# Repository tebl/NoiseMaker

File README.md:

# NoiseMaker
When I first started out with my somewhat weird hobby of working with seriously to extremely outdated computers, the first things to go were naturally the inevitably failing hard-drives that ended up being replaced by Compact Flash solutions. The second to go were the physical floppy disk drives, having been replaced by Gotek drives. The result, while enjoyable to use, were vintage computers that even the wife could even stand to listen to. Except... that's not good, they're supposed to go *whirr*, *click*, *whine* and rotate grinding gears at such a rate that your significant other simply won't just accept a room dedicated to your vintage computers, they should demand that you get started on building such a room!

Was I going back to the old failiure rate of old mechanical drives? Nope, I followed the tutorials and installed a buzzer kit on that Gotek. Was I happy with it? Not really. So I did what I tend to do, go on AliExpress and ordered a bucketload of Arduino-modules listed as capable of playing back sound files. The cheapest of the bunch by far, was the *MP3-TF-16P* - also commonly known as the *DFPlayer Mini*. The very next thing that I discovered was that I didn't really understand enough about the various signals used to communicate with floppy disk drives, so they all sat in box somewhere until someone created something called *HDD Clicker*. I saw the videos made about it, but I wanted more options and so I started tinkering with the modules again - especially with the realization of how simple an IDE-version could have been made if I had just started there instead.

The result was this project, an amalgamation of the cheapest hardware in an oversized package that somehow probably ends up costing several times more to build than the popular thing. I could certainly have gone for more compact or powerful options, but it was an excuse to use some  Arduino Nano boards "powered" by ATmega168, which I had accidentally ordered a couple of years ago and never got around to throwing out.

- [1> Modules](#1-modules)
  - [1.1> NoiseMaker Standard](#11-noisemaker-standard)
- [3> Acknowledgements](#3-acknowledgements)

# 1> Modules
The following modules have been provided as part of this project. While more modules may have been included as part of this repository, these are the ones that I have actually built and tested. As mentioned in the relevant license for this project - that's not a warranty, just an indication that it worked that one time I tried it with my particular setup.

| Module                            | Description                                      |
| --------------------------------- | ------------------------------------------------ | 
| [NoiseMaker Standard](#11-noisemaker-standard) | Standard Arduino-based *NoiseMaker*, supporting 34-pin floppy and 40-pin IDE.

## 1.1> NoiseMaker Standard
This is the standard version of the *NoiseMaker*, created as a carrier board for both the *MP3-TF-16P* and an Arduino Nano. It can be built to work directly with IDE-devices, adding a female 40-pin header to the bottom of the card it can also be attached directly onto common *Compact Flash to IDE*-module. It can also be used in the "middle" of the cable, or just plugged into an unused part of the cable. The Arduino unfortunately doesn't have anywhere near the capability needed to actually interpret the communication between the devices, it is only responding to the same signal that your motherboard would normally read in order to light up your *HDD LED* (if you have one). 

 Alternatively you can build the device for use with 34-pin floppy drive replacements such as the Gotek instead. Similarly as with the IDE-version, it can also be plugged into an unused connector on your cable or in-between your drive and motherboard. Note that since the 34-pin cables have a twist on it, you need to set the *DRV_SEL* to the opposite value if connecting it up by itself after the twist.

The documentation belonging to different variations of the standard NoiseMaker have been listed below, click the name for build documentation or follow the documentation links to jump to different sections within it. Ideally all of them should support being built as a NoiseMaker for either floppy or IDE, but not both at the same time (for that you will need two separate copies of the PCB).

| Module                 | Description                        | Documentation                      | Order      |
| ---------------------- | ---------------------------------- | ---------------------------------- | ---------- |
| [NoiseMaker](https://github.com/tebl/NoiseMaker/tree/main/NoiseMaker) | Arduino Nano, MP3-TF-16P | [Documentation](https://github.com/tebl/NoiseMaker/tree/main/NoiseMaker), [BOM](https://github.com/tebl/NoiseMaker/blob/main/NoiseMaker/README.md#3-bom), [Setting it up](https://github.com/tebl/NoiseMaker/blob/main/documentation/setting_it_up.md), [Getting started](https://github.com/tebl/NoiseMaker/blob/main/documentation/getting_started.md) | PCBWay

# 3> Acknowledgements
Everything comes from something, in particular when it comes to most of my electronics projects. I mainly build things I would like to own, often doing a respin to fit my own particular style and preferences. As mentioned I originally started making a module for making noise when used with modern floppy drive replacements, but it was only with inspiration from seeing the *HDD Clicker* that I went back and actually finished building it.

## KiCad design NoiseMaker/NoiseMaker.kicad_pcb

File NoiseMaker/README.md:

# NoiseMaker Standard
The *NoiseMaker Standard*-version is really the first version I created for making noise when used with either 34-pin floppy drive replacements such as the Gotek - OR - the 40-pin IDE-replacements such as CF2IDE, SD2IDE etc. This document goes into building up a PCB for one of these, but not both at a time. For a more graceful introduction to what the *NoiseMaker* is meant to do, check out the main [documentation](https://github.com/tebl/NoiseMaker) before continuing.

- [1> Building the device](#1-building-the-device)
  - [1.1> Soldering it together](#11-soldering-it-together)
  - [1.2> IDE-version](#12-ide-version)
  - [1.3> Floppy-version](#13-floppy-version)
  - [1.4> Finishing touches](#14-finishing-touches)
- [2> Schematic](#2-schematic)
- [3> BOM](#3-bom)

# 1> Building the device
Building a device such as this assumes you have at least minor experience soldering things together, recommended is that you at the very least have access to a soldering station with adjustable temperature. If currently available, you should probably start with 60/40 rosin core solder as the lead-free alternatives tends to be a bit harder to work with.

With the requirements for basic equipment sorted, we need to talk a bit about what you want to achieve while building this project. The reason I ask is that as already mentioned, you need to pick between Floppy and IDE for each PCB you are building up, mainly because there are physical differences in how each of them connect to the your system. 

Now that you know what you want to build, we can get started on the most expensive step in any build process - shopping! So, head on over to the [BOM](#3-bom)-section for some information on what kind of components that you'll need. While I would have liked to give you specific part numbers for "reputable" electronic part suppliers, I can't afford to shop there so I usually make due with what I can find on sites such as ebay, AliExpress and any similar sites that sell cheap Chinese components. The downside to this is that I can't link to a part directly and expect it to stay listed, so you'll need to consider the description listed as a suggested *search term*.

## 1.1> Soldering it together
The construction of this unit should be fairly straight-forward, just take your time in order to make sure everything goes into place - more or less straight. I usually recommend starting by having a good look at the PCBs, then try to figure out where all of the listed components go and in which orientation they go in (all of this should be clearly marked on the silkscreen). There are no overlapping footprints and though doing it in the wrong order might make it a bit more fiddly to put together, there aren't really all that many issues you can run into as long as you're clear on which interface you're building it for (IDE or floppy). 

## 1.2> IDE-version
I've created a video that goes into whatever details you might need when assembling one for use with IDE, this one specificly was built to mount directly onto a common *Compact Flash*-adapter and for that reason I solder the power wires directly to it instead of using an additional floppy power connector from the systems PSU.

## 1.3> Floppy-version
For now I recommend that you check the build details for the IDE-version, it is mostly the same except for the use of 34-pin Interface.

## 1.4> Finishing touches
Unless one was provided to you by a kit-maker, you will more than likely not have the correct firmware installed on your Arduino Nano. The code you need can be found as part of this repository on the URL [software/arduino/NoiseMaker](https://github.com/tebl/NoiseMaker/tree/main/software/arduino/NoiseMaker), you will need to download a copy of this repository - this is done by using the green button on the [main page](https://github.com/tebl/NoiseMaker) of this repository. You will need to install a couple of libraries in order for the code to compile, the [README](https://github.com/tebl/NoiseMaker/blob/main/software/arduino/NoiseMaker/README.md) contains links to both of these though the preferable way of installing these is probably via your Arduino development environment. The files provided should be suitable for use with both Arduino Studio as well as PlatformIO.

For Arduino Studio, open the sketch and then select the board that you have (Arduino Nano of some kind). Install the two libraries from *Tools* --> *Manage libraries...* - search for and install the two listed as *ezbutton* as well as *DFRobotDFPlayerMini*. Check that the code now compiles, select the serial port corresponding to your module and upload the sketch.

PlatformIO should handle dependencies somewhat automatically, though I find that in practice we need to run a command for it to happen. Open up a new PlatformIO Terminal (not PowerShell, it's probably the last icon on your bottom toolbar), then run the command *"pio pkg install"*, and it should download and install the latest version of the libraries needed. Ensure that the environment selected on the bottom toolbar corresponds to the board you are using, you may need to edit *platformio.ini* if neither of the combinations is correct for you. Compile and upload the code.

Using a serial terminal connected to the Arduino Nano, you may configure the device according to your preferences. It is recommended to use an ATmega328-based Arduino Nano when you are familiarizing yourself with the commands, as among other commands the *help* command is not available on the ATmega168. When satisfied with any changes, enter the command *save* to store them permanently to the onboard EEPROM. For more detailed information as well as serving as a reference when used with ATmega168, see [Serial Interface](https://github.com/tebl/NoiseMaker/blob/main/documentation/serial_interface.md).

# 2> Schematic
The supplied KiCad files should be sufficient as both a schematic and as a  starting point for ordering PCBs (basically you could just zip the contents of the export folder and upload that on a fabrication site), the schematic is also available in [PDF-format](https://github.com/tebl/NoiseMaker/tree/main/documentation/schematic) and this is what you'll need to print and work your way through this things don't work as expected after assembly.

# 3> BOM
Most parts should be easy to get a hold of from your favourite local electronic component shop, but given that I don't have access to such shops where I live so everything was based on whatever I could get cheapest from eBay/AliExpress (free shipping, but plan on waiting 3-4 weeks for delivery). Components in parenthesis can be considered optional for features beyond the more basic functionality, but where's the fun in that? You probably want the complete package.

| Reference             | Item                                                              | Count | Order  |
| --------------------- | ----------------------------------------------------------------- | ----- | ------ |
| NoiseMaker Standard   | Fabricate using Gerber files                                      |     1 | [PCBWay](https://www.pcbway.com/project/shareproject/NoiseMaker_IDE_Floppy_8a4ab037.html)
| A1 *                  | Arduino Nano (328, 168 with less features)                        |     1 |
| A2 *                  | MP3-TF-16P (also known as DFPlayer Mini)                          |     1 |
| D1                    | 1N5819 (DO-41), 1N4001 if you don't have one available            |     1 |
| J1 **                 | 2x20pin female header, 2x20pin male header or 2x17pin male header |     1 |
| J2 **                 | 2x20pin male header or 2x17pin male header                        |     1 |
| J3 ***                | JVC Mini 4P, right-angle flat power connector for floppy          |     1 |
| J4                    | 4pin breakable right-angle header                                 |    (1)|
| JP1, JP2              | 3pin straight pin header                                          |     2 |
|                       | Jumper cap                                                        |     2 |
| LS1                   | Passive buzzer (7.62mm pin spacing)                               |    (1)|
| R1                    | 1k Ohm resistor                                                   |     1 |
| SW1-SW3               | 6x6mm momentary button                                            |    (3)|

*) Both of the modules will be soldered to the PCB with some straight male headers in between, when assembling the first unit it is recommend that you assemble it with female pin headers on the board so that modules can be moved around until happy with the results.

**) The type of header used here depends on what the board will be used as, 2x16pin are for floppy while 2x20pin are for IDE.

***) When installed directly on top of a Compact Flash adapter you can opt to wire it directly to the adapter. If you can't find the connector, it might be easier to find a floppy power splitter cable, cut and solder on the wires from that.

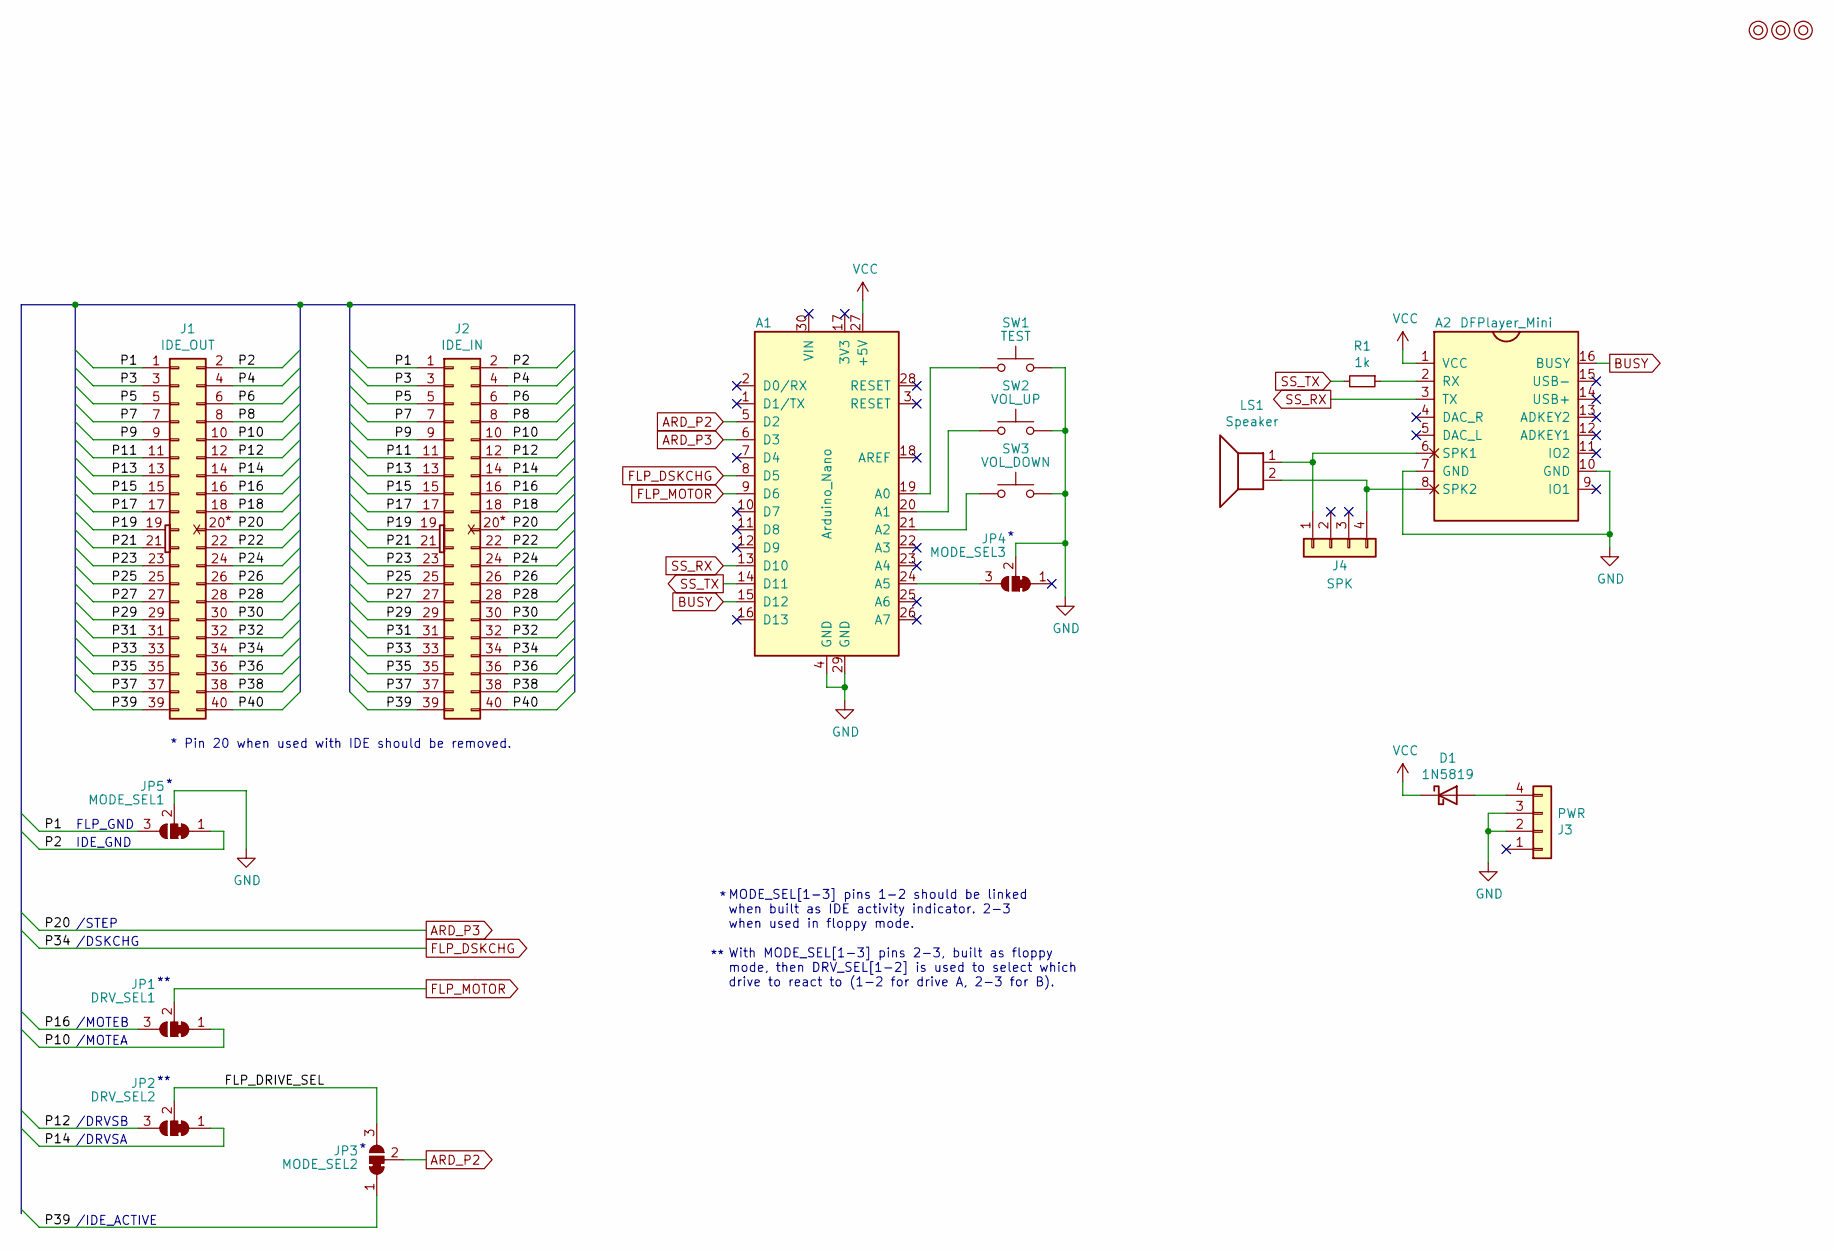
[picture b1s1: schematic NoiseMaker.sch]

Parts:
A1: Arduino_Nano
A2: DFPlayer_Mini
D1: 1N5819; D_DO-41_SOD81_P12.70mm_Horizontal
J1: IDE_OUT; PinSocket_2x20_P2.54mm_Vertical
J2: IDE_IN; IDC-Header_2x20_P2.54mm_Vertical
J3: PWR; Molex_KK-254_1x04_P2.54mm_Horizontal
J4: SPK; PinHeader_1x04_P2.54mm_Horizontal
JP1: DRV_SEL1; PinHeader_1x03_P2.54mm_Vertical
JP2: DRV_SEL2; PinHeader_1x03_P2.54mm_Vertical
JP3: MODE_SEL2; select2
JP4: MODE_SEL3; select2
JP5: MODE_SEL1; select2
LS1: Speaker; Buzzer_12x9.5RM7.6
M1, M2, M3: Mounting; M3_pin
R1: 1k; R_Axial_DIN0207_L6.3mm_D2.5mm_P10.16mm_Horizontal
SW1: TEST; SW_PUSH_6mm
SW2: VOL_UP; SW_PUSH_6mm
SW3: VOL_DOWN; SW_PUSH_6mm

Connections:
/FLP_DRIVE_SEL: JP2.2 (C), JP3.3 (B)
/P1: J1.1, J2.1, JP5.3 (B)
/P2: J1.2, J2.2, JP5.1 (A)
/P3: J1.3, J2.3
/P4: J1.4, J2.4
/P5: J1.5, J2.5
/P6: J1.6, J2.6
/P7: J1.7, J2.7
/P8: J1.8, J2.8
/P9: J1.9, J2.9
/P10: J1.10, J2.10, JP1.1 (A)
/P11: J1.11, J2.11
/P12: J1.12, J2.12, JP2.3 (B)
/P13: J1.13, J2.13
/P14: J1.14, J2.14, JP2.1 (A)
/P15: J1.15, J2.15
/P16: J1.16, J2.16, JP1.3 (B)
/P17: J1.17, J2.17
/P18: J1.18, J2.18
/P19: J1.19, J2.19
/P21: J1.21, J2.21
/P22: J1.22, J2.22
/P23: J1.23, J2.23
/P24: J1.24, J2.24
/P25: J1.25, J2.25
/P26: J1.26, J2.26
/P27: J1.27, J2.27
/P28: J1.28, J2.28
/P29: J1.29, J2.29
/P30: J1.30, J2.30
/P31: J1.31, J2.31
/P32: J1.32, J2.32
/P33: J1.33, J2.33
/P35: J1.35, J2.35
/P36: J1.36, J2.36
/P37: J1.37, J2.37
/P38: J1.38, J2.38
/P39: J1.39, J2.39, JP3.1 (A)
/P40: J1.40, J2.40
ARD_P2: A1.5 (D2), JP3.2 (C)
ARD_P3: A1.6 (D3), J1.20, J2.20
BUSY: A1.15 (D12), A2.16 (BUSY)
FLP_DSKCHG: A1.8 (D5), J1.34, J2.34
FLP_MOTOR: A1.9 (D6), JP1.2 (C)
GND: A1.4 (GND), A1.29 (GND), A2.7 (GND), A2.10 (GND), J3.2, J3.3, JP4.2 (C), JP5.2 (C), SW1.2, SW2.2, SW3.2
unnamed: A1.19 (A0), SW1.1
unnamed: A1.20 (A1), SW2.1
unnamed: A1.21 (A2), SW3.1
unnamed: A1.24 (A5), JP4.3 (B)
unnamed: A2.2 (RX), R1.1
unnamed: A2.6 (SPK1), J4.1, LS1.1
unnamed: A2.8 (SPK2), J4.4, LS1.2
unnamed: D1.2 (A), J3.4
SS_RX: A1.13 (D10), A2.3 (TX)
SS_TX: A1.14 (D11), R1.2
VCC: A1.27 (+5V), A2.1 (VCC), D1.1 (K)

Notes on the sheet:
/DRVSA
/DRVSB
/MOTEA
/MOTEB
/IDE_ACTIVE
/STEP
/DSKCHG
* Pin 20 when used with IDE should be removed.
IDE_GND
FLP_GND
MODE_SEL[1-3] pins 1-2 should be linked when built as IDE activity indicator. 2-3 when used in floppy mode.
With MODE_SEL[1-3] pins 2-3, built as floppy mode, then DRV_SEL[1-2] is used to select which drive to react to (1-2 for drive A, 2-3 for B).

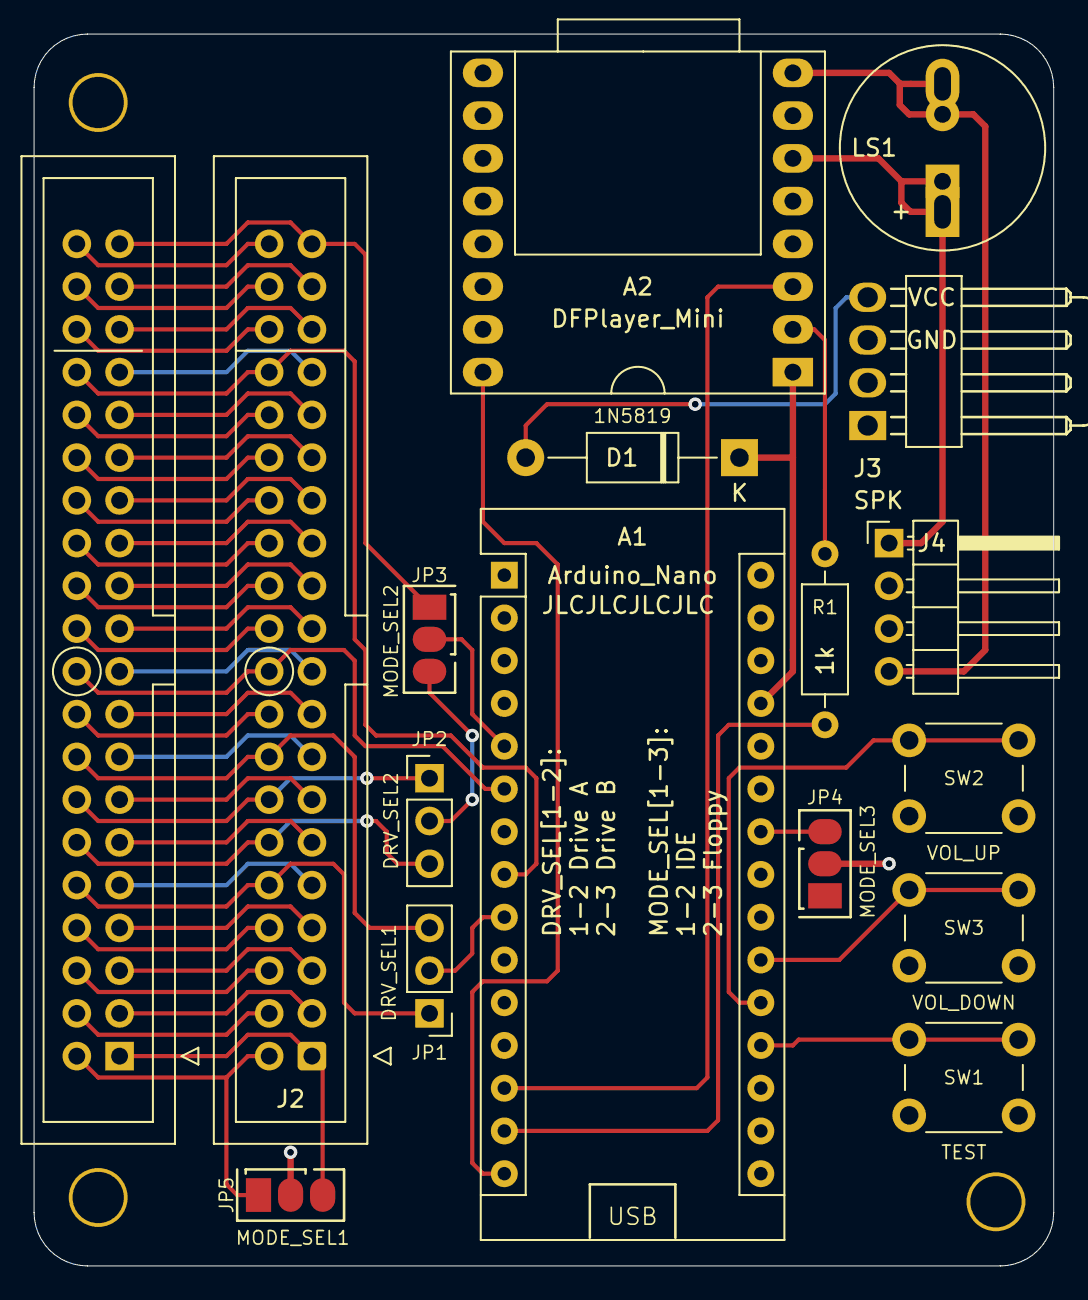
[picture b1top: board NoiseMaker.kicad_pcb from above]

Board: 2 copper layers, 60.6 x 73.2 mm, 20 parts (1 on the bottom side), 56 nets.

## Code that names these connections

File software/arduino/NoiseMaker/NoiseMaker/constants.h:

#pragma once

/* Magic numbers */
#define BAUD_RATE_115200 115200
#define BAUD_RATE_38400 38400
#define BAUD_RATE_19200 19200
#define BAUD_RATE_9600 9600
#define BAUD_RATE_4800 4800
#define BAUD_RATE BAUD_RATE_115200

#define TERMINAL_COLS 80

#define MODE_IDE 0
#define MODE_FLOPPY 1

#define STATE_INIT 0
#define STATE_FLP_IDLE 1
#define STATE_FLP_SPINNING 2
#define STATE_FLP_ACTIVE 3

#define STATE_IDE_IDLE 10
#define STATE_IDE_ACTIVE 11
#define STATE_IDE_PAUSED 12

#define SOUND_IDE_STARTUP 1
#define SOUND_IDE_ACTIVE 2
#define SOUND_IDE_SHUTDOWN 3
#define SOUND_FLP_STARTUP 1
#define SOUND_FLP_SPIN 2
#define SOUND_FLP_SNATCH 3
#define SOUND_FLP_CLICK 4

#define ONE_MINUTE 60000L
#define TEN_MINUTES 600000L
#define FIFTEEN_MINUTES 900000L

#define OFFSET_FLOPPY 1
#define OFFSET_IDE 10

/* Pin definitions */
#define DFPlayer_TX 11
#define DFPlayer_RX 10
#define DFPlayer_BUSY 12
#define PIN_TEST A0
#define PIN_VOL_UP A1
#define PIN_VOL_DOWN A2
#define PIN_MODE_SEL A5
#define PIN_ARD_P2 2
#define PIN_ARD_P3 3

#define PIN_IDE_ACTIVE PIN_ARD_P2
#define PIN_FLP_DRIVE_SEL PIN_ARD_P2
#define PIN_FLP_STEP PIN_ARD_P3
#define PIN_FLP_DISK_CHANGE 5
#define PIN_FLP_MOTOR_EN 6
#define PIN_LED LED_BUILTIN

/* Volume values */
#define VOLUME_1 10
#define VOLUME_2 15
#define VOLUME_3 20
#define VOLUME_4 22
#define VOLUME_5 24
#define VOLUME_6 26
#define VOLUME_7 28
#define VOLUME_8 31

/* Strings for reuse */
#define APP_TITLE "NoiseMaker"
#define APP_VERSION "0.1"
const char STR_DONE[] PROGMEM  = "done!";
const char STR_ERROR_ARGUMENT[] PROGMEM = "argument format";
const char STR_ERROR_DFPLAYER[] PROGMEM = "DFPlayer ERROR ";

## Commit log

2022-10-18 Initial layout
2022-10-18 Add test button
2022-11-01 Tweak silkscreen and dimensions
2022-11-06 First attempt at sketch
2022-11-06 Still replay issues
2022-11-06 Tweaks
2022-11-20 Add proper power connector and more switches
2022-11-20 Try to squash bug where it is stuck on
2022-11-21 Add shutdown sound and profile commands
2022-11-24 Some features only on 328
2022-11-24 Threshold values in EEPROM
2022-11-24 Debug statements can be compiled out
2022-11-24 Refactoring
2022-11-24 And some more
2022-11-26 First floppy attempt
2022-11-26 Datasheets added
2022-11-26 Refer to volume levels consistently
2022-11-26 Can set threshold values
2022-11-27 Change defaults
2022-11-27 Add profile sounds
2022-11-27 Fixed error message
2022-11-28 Rename project files
2022-11-29 Add images
2022-11-30 Some documentation stubbed out
2022-11-30 Some empty documentation
2022-11-30 List libraries used
2022-11-30 Parts list
2022-11-30 JP2 now THT jumper
2022-11-30 Account for two common passive buzzers
2022-11-30 Missing files
2022-11-30 Did it properly
2022-12-01 Rename library
2022-12-31 Missing library dependency
2022-12-31 Update README and tweak silkscreen
2023-01-14 Add video image
2023-01-14 Add video link
2023-01-14 Update link image

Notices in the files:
NoiseMaker/NoiseMaker.kicad_pcb:
Licensed under CERN OHL v1.2
